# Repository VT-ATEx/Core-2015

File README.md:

# Core-2015
2015-2016 School Year

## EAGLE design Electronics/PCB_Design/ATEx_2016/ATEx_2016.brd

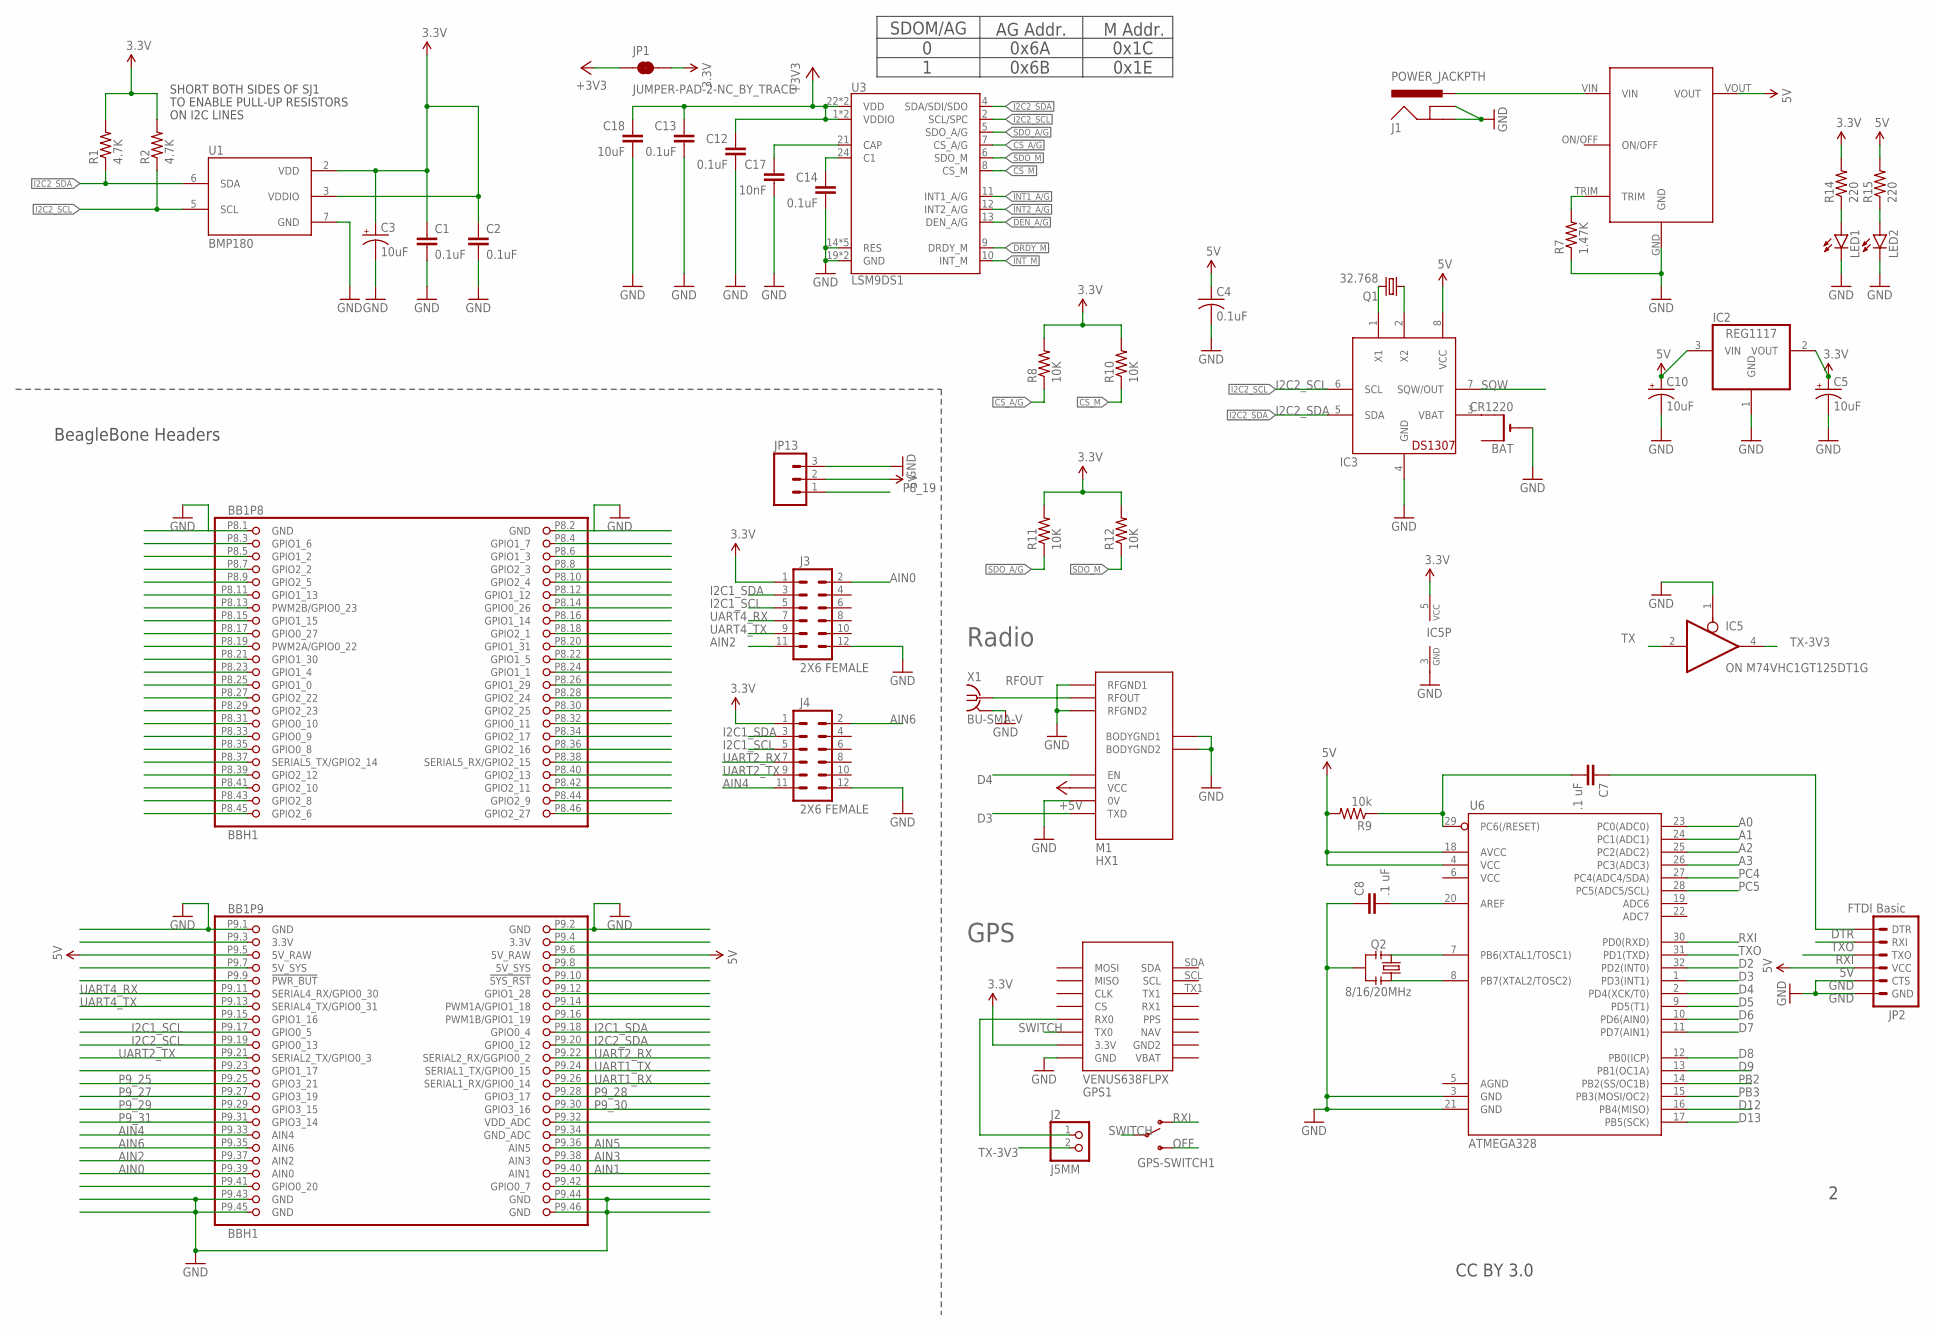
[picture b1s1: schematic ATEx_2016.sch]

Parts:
BAT: CR1220; CR1220-THM
BB1: BBH1; BB_CAPE
C1, C2, C12, C13, C14: 0.1uF; 0603-CAP
C3, C5, C10: 10uF; EIA3216
C4: 0.1uF; C0603
C7, C8: .1 uF; 0603-CAP
C17: 10nF; 0603-CAP
C18: 10uF; 0603-CAP
GPS1: VENUS638FLPX
GPS-SWITCH1: SWITCH-SPSTPTH; SWITCH-SPDT
IC2: REG1117; SOT223; PARTNO *
IC3: DS1307; DIL08
IC5: ON M74VHC1GT125DT1G; SOT23-5
J1: POWER_JACKPTH; POWER_JACK_PTH
J2: J5MM; 1X02
J3, J4: 2X6 FEMALE; 2X6
JP1: JUMPER-PAD-2-NC_BY_TRACE; PAD-JUMPER-2-NC_BY_TRACE_YES_SILK
JP2: FTDI Basic; 1X06
JP13: M03PTH; 1X03
LED1, LED2: LED-FKIT-1206; FKIT-LED-1206
M1: HX1
Q1: 32.768; TC38H
Q2: 8/16/20MHz; RESONATOR-SMD
R1, R2: 4.7K; 0603-RES
R7: 1.47K; R0603; PARTNO *
R8, R10, R11, R12: 10K; 0603-RES
R9: 10k; 0603-RES
R14, R15: 220; R0603; PARTNO *
U1: BMP180
U3: LSM9DS1; LGA24-8X4
U6: ATMEGA328; TQFP32-08
U$1: DNT12S0A0S03NFA; SMD
X1: BU-SMA-V

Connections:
3.3V: C1.1, C2.1, C3.A (+), C5.A (+), GPS1.3.3V, IC2.2 (VOUT), IC5.5 (VCC), J3.1, J4.1, JP1.2, R1.2, R2.2, R8.2, R10.2, R11.2, R12.2, R14.2, U1.2 (VDD), U1.3 (VDDIO)
3VOLT: LED1.A, R14.1
5V: BB1.P9.5 (5V_RAW), BB1.P9.6 (5V_RAW), C4.1, C10.A (+), IC2.3 (VIN), IC3.8 (VCC), JP2.4 (VCC), JP13.2, R9.2, R15.2, U6.4 (VCC), U6.18 (AVCC), U$1.VOUT
5VOLT: LED2.A, R15.1
+3V3: C12.1, C13.1, C18.1, JP1.1, U3.1 (VDDIO), U3.3 (VDDIO), U3.22 (VDD), U3.23 (VDD)
+5V: M1.VCC
A0: U6.23 (PC0(ADC0))
A1: U6.24 (PC1(ADC1))
A2: U6.25 (PC2(ADC2))
A3: U6.26 (PC3(ADC3))
AIN0: BB1.P9.39 (AIN0), J3.2
AIN1: BB1.P9.40 (AIN1)
AIN2: BB1.P9.37 (AIN2), J3.11
AIN3: BB1.P9.38 (AIN3)
AIN4: BB1.P9.33 (AIN4), J4.11
AIN5: BB1.P9.36 (AIN5)
AIN6: BB1.P9.35 (AIN6), J4.2
C2: C14.1, U3.24 (C1)
CAP1: C17.1, U3.21 (CAP)
CS_A/G: R8.1, U3.7 (CS_A/G)
CS_M: R10.1, U3.8 (CS_M)
D2: U6.32 (PD2(INT0))
D3: M1.TXD, U6.1 (PD3(INT1))
D4: M1.EN, U6.2 (PD4(XCK/T0))
D5: U6.9 (PD5(T1))
D6: U6.10 (PD6(AIN0))
D7: U6.11 (PD7(AIN1))
D8: U6.12 (PB0(ICP))
D9: U6.13 (PB1(OC1A))
D12: U6.16 (PB4(MISO))
D13: U6.17 (PB5(SCK))
DEN_A/G: U3.13 (DEN_A/G)
DRDY_M: U3.9 (DRDY_M)
DTR: C7.1, JP2.1 (DTR)
GND: BAT.-, BB1.P8.1 (GND), BB1.P8.2 (GND), BB1.P9.1 (GND), BB1.P9.2 (GND), BB1.P9.43 (GND), BB1.P9.44 (GND), BB1.P9.45 (GND), BB1.P9.46 (GND), C1.2, C2.2, C3.C (-), C4.2, C5.C (-), C8.1, C10.C (-), C12.2, C13.2, C14.2, C17.2, C18.2, GPS1.GND, IC2.1 (GND), IC3.4 (GND), IC5.1 (OE), J1.GND, J1.GNDBREAK, J3.12, J4.12, JP2.5 (CTS), JP2.6 (GND), JP13.3, LED1.C, LED2.C, M1.0V, M1.BODYGND1, M1.BODYGND2, M1.RFGND1, M1.RFGND2, Q2.2, R7.1, U1.7 (GND), U3.14 (RES), U3.15 (RES), U3.16 (RES), U3.17 (RES), U3.18 (RES), U3.19 (GND), U3.20 (GND), U6.3 (GND), U6.21 (GND), U$1.GND, X1.2 (GND), X1.3 (GND), X1.4 (GND), X1.5 (GND)
I2C1_SCL: BB1.P9.17 (GPIO0_5), J3.5, J4.5
I2C1_SDA: BB1.P9.18 (GPIO0_4), J3.3, J4.3
I2C2_SCL: BB1.P9.19 (GPIO0_13), IC3.6 (SCL), R2.1, U1.5 (SCL), U3.2 (SCL/SPC)
I2C2_SDA: BB1.P9.20 (GPIO0_12), IC3.5 (SDA), R1.1, U1.6 (SDA), U3.4 (SDA/SDI/SDO)
INT1_A/G: U3.11 (INT1_A/G)
INT2_A/G: U3.12 (INT2_A/G)
INT_M: U3.10 (INT_M)
unnamed: J1.PWR, U$1.VIN
unnamed: R7.2, U$1.TRIM
unnamed: Q2.3, U6.7 (PB6(XTAL1/TOSC1))
unnamed: Q2.1, U6.8 (PB7(XTAL2/TOSC2))
unnamed: IC3.1 (X1), Q1.2
unnamed: GPS1.RX0, J2.1
unnamed: C8.2, U6.20 (AREF)
unnamed: IC3.2 (X2), Q1.1
unnamed: C7.2, R9.1, U6.29 (PC6(/RESET))
unnamed: BAT.+2 (+1), IC3.3 (VBAT)
OFF: GPS-SWITCH1.3 (S)
P8_11: BB1.P8.11 (GPIO1_13)
P8_12: BB1.P8.12 (GPIO1_12)
P8_19: BB1.P8.19 (PWM2A/GPIO0_22), JP13.1
P9_25: BB1.P9.25 (GPIO3_21)
P9_27: BB1.P9.27 (GPIO3_19)
P9_28: BB1.P9.28 (GPIO3_17)
P9_29: BB1.P9.29 (GPIO3_15)
P9_30: BB1.P9.30 (GPIO3_16)
P9_31: BB1.P9.31 (GPIO3_14)
P9_41: BB1.P9.41 (GPIO0_20)
P9_42: BB1.P9.42 (GPIO0_7)
PB2: U6.14 (PB2(SS/OC1B))
PB3: U6.15 (PB3(MOSI/OC2))
PC4: U6.27 (PC4(ADC4/SDA))
PC5: U6.28 (PC5(ADC5/SCL))
RFOUT: M1.RFOUT, X1.1
RXI: GPS-SWITCH1.1 (O), JP2.3 (TXO), U6.30 (PD0(RXD))
SDO_A/G: R11.1, U3.5 (SDO_A/G)
SDO_M: R12.1, U3.6 (SDO_M)
SQW: IC3.7 (SQW/OUT)
SWITCH: GPS1.TX0, GPS-SWITCH1.2
TX: IC5.2 (I)
TX-3V3: IC5.4 (O), J2.2
TXO: JP2.2 (RXI), U6.31 (PD1(TXD))
UART1_RX: BB1.P9.26 (SERIAL1_RX/GPIO0_14)
UART1_TX: BB1.P9.24 (SERIAL1_TX/GPIO0_15)
UART2_RX: BB1.P9.22 (SERIAL2_RX/GGPIO0_2), J4.7
UART2_TX: BB1.P9.21 (SERIAL2_TX/GPIO0_3), J4.9
UART4_RX: BB1.P9.11 (SERIAL4_RX/GPIO0_30), J3.7
UART4_TX: BB1.P9.13 (SERIAL4_TX/GPIO0_31), J3.9

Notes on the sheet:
BeagleBone Headers
CC BY 3.0
Radio
GPS
SHORT BOTH SIDES OF SJ1
TO ENABLE PULL-UP RESISTORS
ON I2C LINES
SDOM/AG
0x1C 0x1E
AG Addr.
0 1
M Addr.
0x6A 0x6B

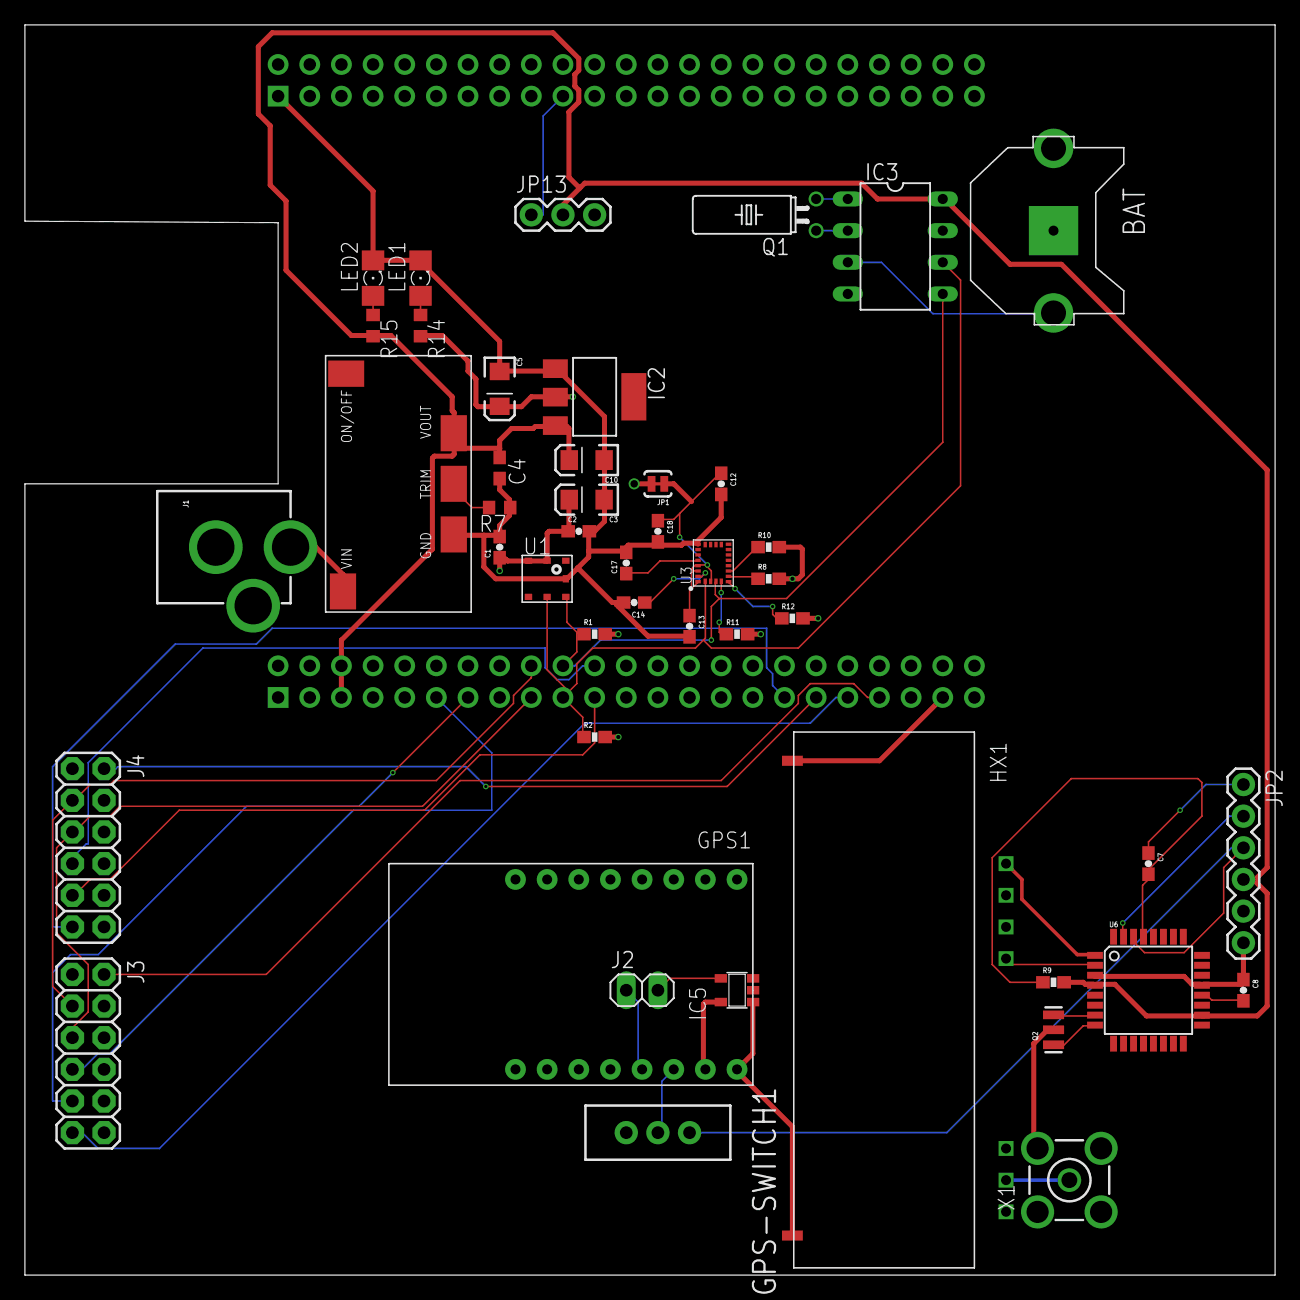
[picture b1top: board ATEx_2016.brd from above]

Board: 4 copper layers, 100.3 x 100.3 mm, 47 parts (0 on the bottom side), 43 nets.

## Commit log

2016-01-31 Added PCB
2016-02-22 Added components
2016-03-01 Finalized PCB design

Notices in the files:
parts and their libraries:
SparkFun-Capacitors: Licensing: CC v3.0 Share-Alike You are welcome to use this library for commercial purposes.
SparkFun-Connectors: Licensing: Creative Commons ShareAlike 4.0 International - https://creativecommons.org/licenses/by-sa/4.0
